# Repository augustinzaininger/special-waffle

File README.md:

# special-waffle
A collection of things I've made that may be useful, or may not be\
GitHub suggested the name and I went with it.

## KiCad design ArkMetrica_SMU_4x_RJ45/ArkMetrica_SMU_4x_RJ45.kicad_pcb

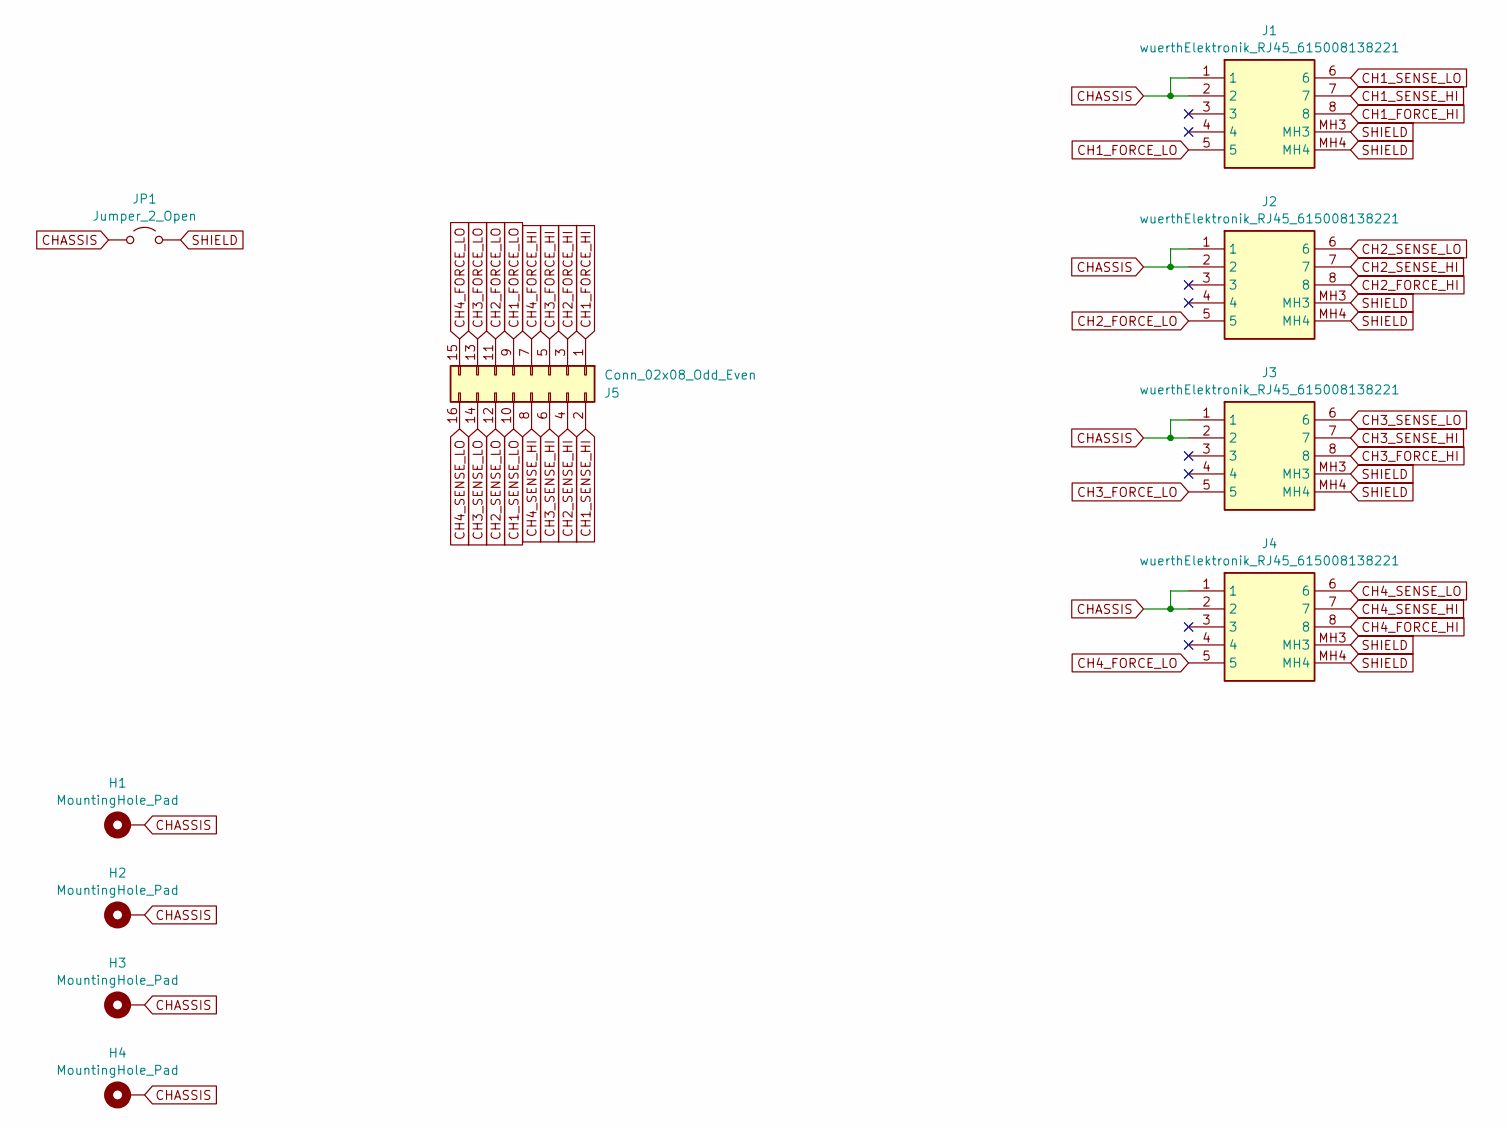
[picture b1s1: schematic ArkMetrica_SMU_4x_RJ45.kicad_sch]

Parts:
H1, H2, H3, H4: MountingHole_Pad; MountingHole_4.3mm_M4_Pad_Via
J1, J2, J3, J4: wuerthElektronik_RJ45_615008138221; Manufacturer_Part_Number 615008138221
J5: Conn_02x08_Odd_Even; shieldedHeader_2x8_SHDR16W56P254_2X8_2782X850X950P
JP1: Jumper_2_Open; SolderJumper-2_P1.3mm_Open_TrianglePad1.0x1.5mm

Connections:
CH1_FORCE_HI: J1.8, J5.1
CH1_FORCE_LO: J1.5, J5.9
CH1_SENSE_HI: J1.7, J5.2
CH1_SENSE_LO: J1.6, J5.10
CH2_FORCE_HI: J2.8, J5.3
CH2_FORCE_LO: J2.5, J5.11
CH2_SENSE_HI: J2.7, J5.4
CH2_SENSE_LO: J2.6, J5.12
CH3_FORCE_HI: J3.8, J5.5
CH3_FORCE_LO: J3.5, J5.13
CH3_SENSE_HI: J3.7, J5.6
CH3_SENSE_LO: J3.6, J5.14
CH4_FORCE_HI: J4.8, J5.7
CH4_FORCE_LO: J4.5, J5.15
CH4_SENSE_HI: J4.7, J5.8
CH4_SENSE_LO: J4.6, J5.16
CHASSIS: H1.1, H2.1, H3.1, H4.1, J1.1, J1.2, J2.1, J2.2, J3.1, J3.2, J4.1, J4.2, JP1.1 (A)
SHIELD: J1.MH3, J1.MH4, J2.MH3, J2.MH4, J3.MH3, J3.MH4, J4.MH3, J4.MH4, JP1.2 (B)

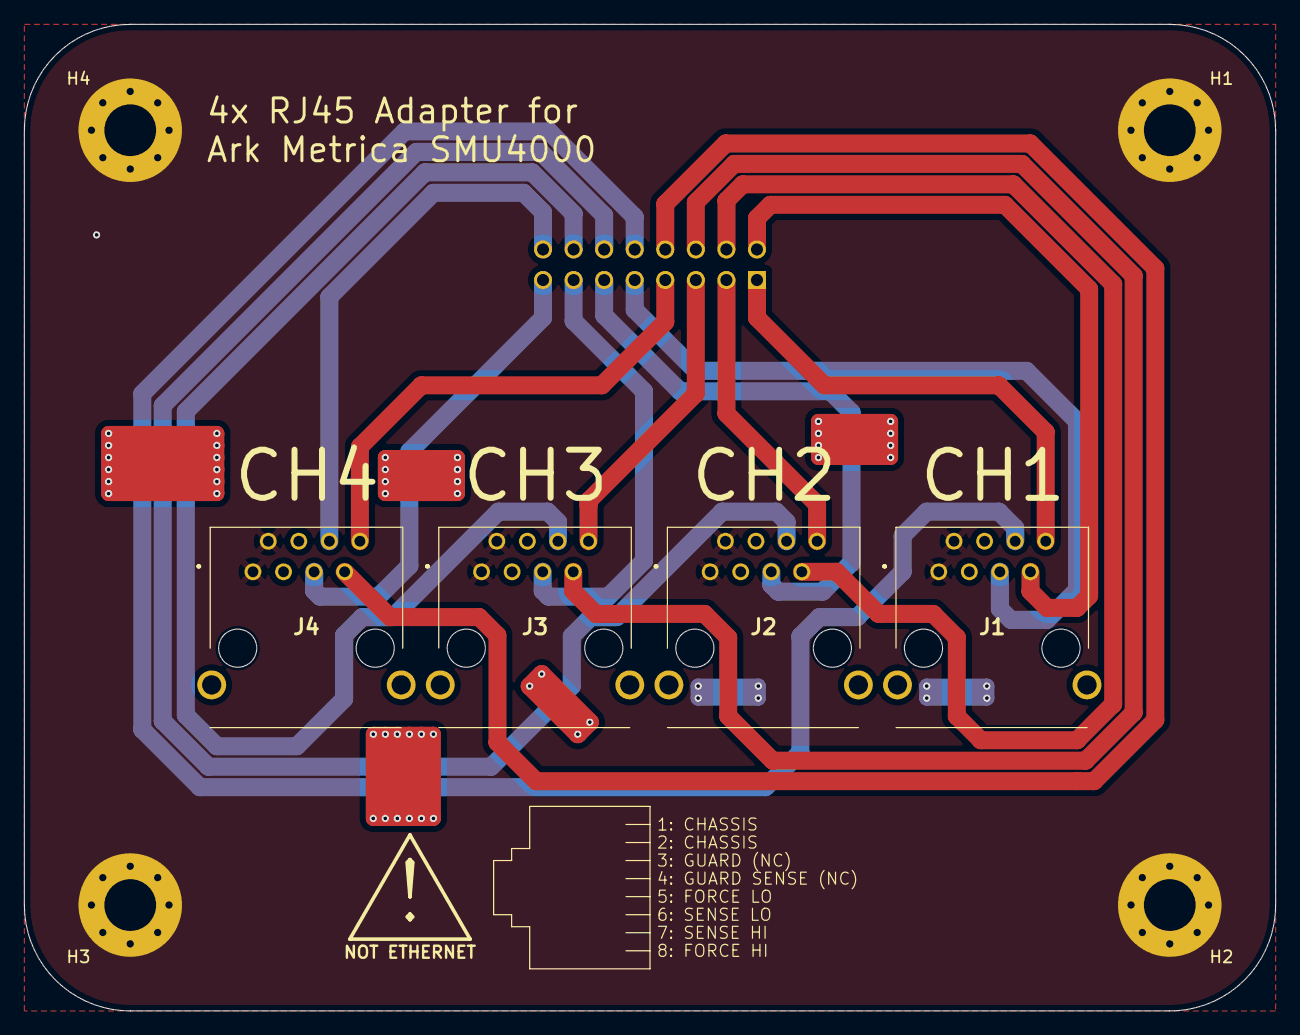
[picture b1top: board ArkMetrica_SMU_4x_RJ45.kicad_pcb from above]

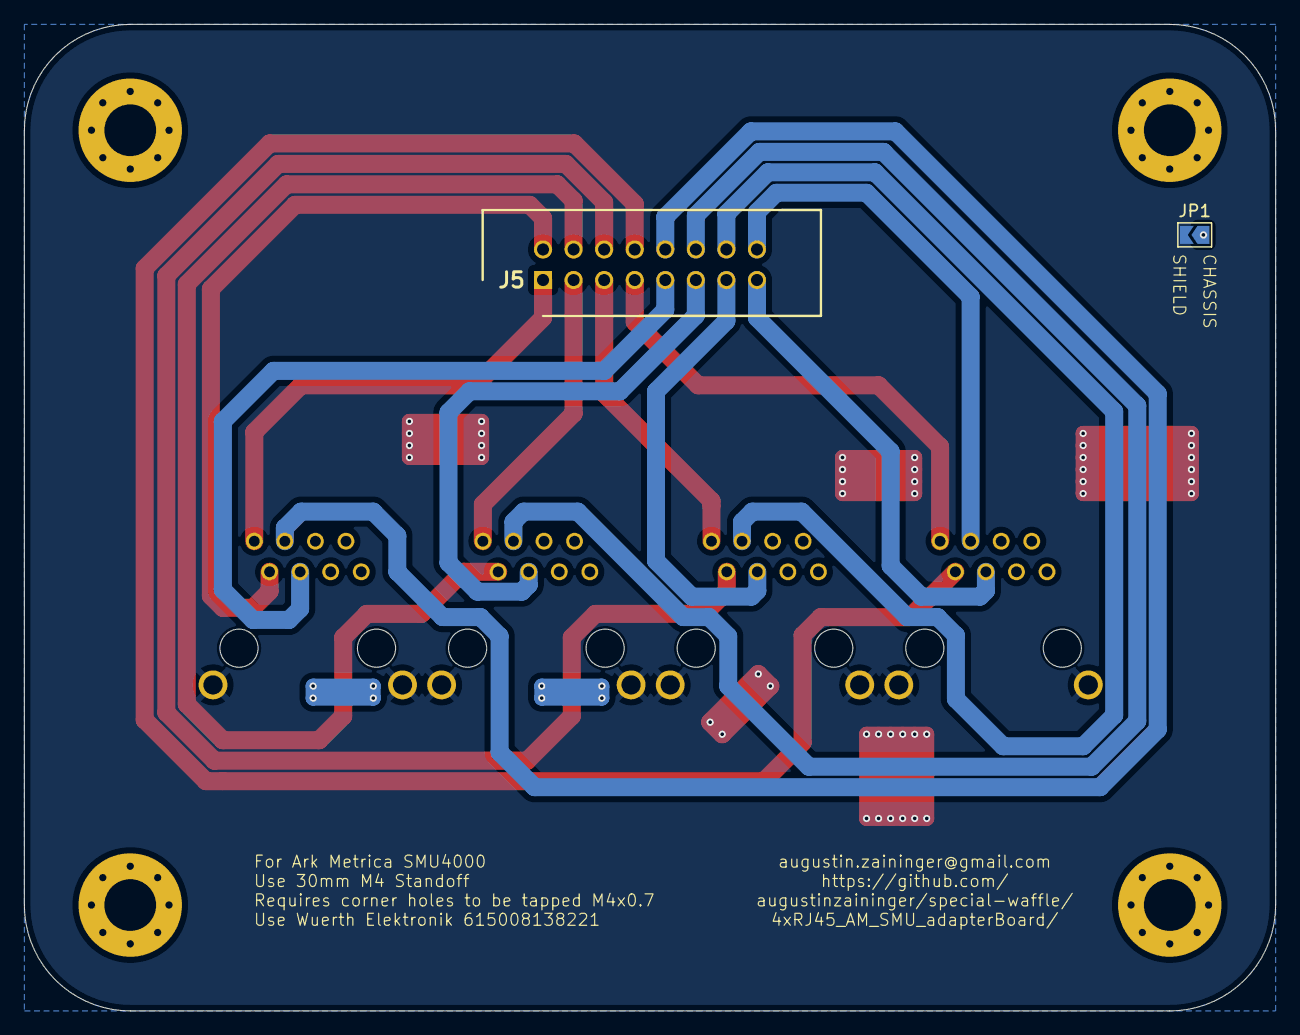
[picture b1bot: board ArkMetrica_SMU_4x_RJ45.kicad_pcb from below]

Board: 2 copper layers, 104.0 x 82.0 mm, 10 parts (2 on the bottom side), 18 nets.

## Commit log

2026-04-28 Added Ark Metrica SMU - 4x RJ45 PCB
